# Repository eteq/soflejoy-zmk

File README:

# Soflejoy

This is a mod on a Sofle Choc keyboard that replaces the right-side encoder with a joystick.  The PCB layout for the adapter board is a KiCad PCB in ``joystick_encoder_adapter``. The joystick is a FJ06K-S joystick and you can just solder that into the adapter board and then use short lengths of wire to connect the adapter to the encoder footprint. Note, though, there is not a power pin available on the existing Sofle layout, so you will need to do a little bodge wire connecting the 3V pad on the adapter to the nearby 3V pad for the power jack that connects the two halves of the keyboard.

## Building

In zmk dir, start devcontainer as:

% devcontainer up --workspace-folder ~/src/zmk && devcontainer exec --workspace-folder ~/src/zmk bash

Then in the devcontainer:

% cd app
% west build -d build/left -b nice_nano_v2 -- -DSHIELD=soflejoy_left -DZMK_CONFIG=/workspaces/zmk-config -DZMK_EXTRA_MODULES=/workspaces/zmk-config && west build -d build/right -b nice_nano_v2 -- -DSHIELD=soflejoy_right -DZMK_CONFIG=/workspaces/zmk-config -DZMK_EXTRA_MODULES=/workspaces/zmk-config

But that only works if the zmk-config volume is set up to point to this directory.

## Joystick calibration

For in-min/max/deadzone values I set are probably dependent on the specific joystick. To determine them I compiled the right board with ``-S zmk-usb-logging``, set ``config INPUT_LOG_LEVEL=4`` in the defconfig, and then fiddled with the joystick while saving out the ttyACM0 output.  I then parsed the raw values with some manual python to get the resulting values. For my particular joystick I saw:

* both x and y would max out at ~4000 if you just scrolled them, but if you wiped them, went up to ~4050
* x and y both mined out within 10 or so of 0, although x consistently at -3, and y either 10 or -3 depending on wiping
* x at center seemed to be 2010 - 2030
* y at center seemed to be 1780 - 2100 - i.e. didn't bounce back to the same spot
* std at stability was ~4

## Modifying the keymap

The keymap is configured via the ``boards/shields/soflejoy/sofle_keymaps.xlsx file``.  Once updated, run ``python make_map.py -f sofle_keymaps.xlsx > soflejoy.keymap`` to update the keymap.

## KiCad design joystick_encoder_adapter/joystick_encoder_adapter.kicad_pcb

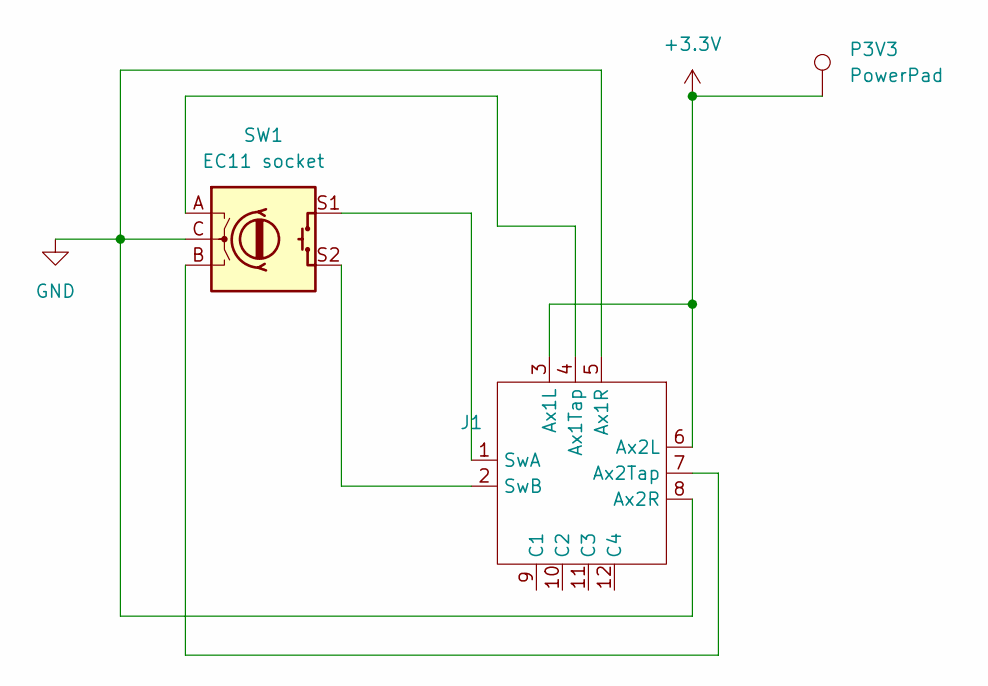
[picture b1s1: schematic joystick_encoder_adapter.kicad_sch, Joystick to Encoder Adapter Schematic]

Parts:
J1: FJ06K
P3V3: PowerPad; TestPoint_THTPad_D2.0mm_Drill1.0mm
SW1: EC11 socket; ec11e_from_sofle_nomp

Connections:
+3.3V: J1.3 (Ax1L), J1.6 (Ax2L), P3V3.1
GND: J1.5 (Ax1R), J1.8 (Ax2R), SW1.C
unnamed: J1.4 (Ax1Tap), SW1.A
unnamed: J1.7 (Ax2Tap), SW1.B
unnamed: J1.1 (SwA), SW1.S1
unnamed: J1.2 (SwB), SW1.S2

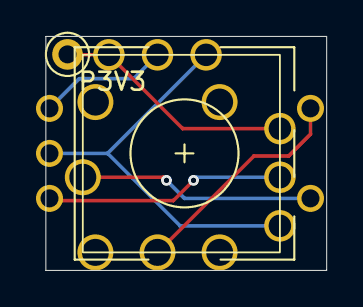
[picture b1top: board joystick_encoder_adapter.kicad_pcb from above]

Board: 2 copper layers, 15.6 x 13.0 mm, 3 parts (0 on the bottom side), 6 nets.

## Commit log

2025-02-09 initial import from testing zmk branch
    note that this is actually the contents of a separate branch
    eteq/zmk@eriks_custom, SHA f817a88fcb2073223114d52b8043c3019313654f,
    but it was going to screw up history a lot to try to merge that in
    here.
2025-02-09 back to orig layout file
2025-02-10 fix key changes in Kconfig
2025-02-10 silly whitespace
2025-02-14 should be working joystick layer but with moody dts
2025-02-15 import analog_axis from zephyr main branch and integrate
    commit is https://github.com/zephyrproject-rtos/zephyr/commit/ff4dc62f0e523c471516349d150531b0cb3c7d1e
2025-02-15 add readme with some build info
2025-02-15 add joystick encoder adapter
2025-02-15 gitig
2025-02-17 semi-working joystick
2025-02-18 working joystick axis
2025-02-28 working stick
2025-03-02 improve joystick behavior
2025-03-02 fix for adc behavior (requiring manual patch)
2025-03-02 dirty calib script
2025-03-02 clean up configs
